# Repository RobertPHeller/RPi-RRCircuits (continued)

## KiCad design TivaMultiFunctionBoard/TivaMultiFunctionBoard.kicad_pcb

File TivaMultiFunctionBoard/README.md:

# TivaMultiFunctionBoard

This is a circuit board that supports a Tiva LaunchPad MCU to manage a range
of possible interlocking plants or other model railroad situations. It
contains four stall motor drivers with point sense, four CT Coil type
occupancy detectors, four Schmitt-Trigger inputs (for push buttons), four
driver outputs, 8 GPIO pins in a 5x2 header, and 16 PWM LED drivers. 
                                                  
The board contains these I/O sections:

- Four occupancy detectors.  These are current transformer based for DCC.
- Four stall-motor with point sense.
- Four Schmitt-Trigger inputs, typically for facia push buttons.
- Four driver outputs, typically for facia lamps (LEDs).
- Eight GPIO pins brought out to a 5x2 header.
- Sixteen PWM Led drivers.  These are meant to light lamps in signal heads. 

This board uses 24 GPIO pins and one I2C channel:

- **PD7** OD1
- **PF4** OD2
- **PA5** OD3
- **PB2** OD4
- **PC5** Motor1
- **PC6** Motor2
- **PC7** Motor3
- **PD6** Motor4
- **PF2** Points1
- **PF3** Points2
- **PB3** Points3
- **PC4** Points4
- **PD0** LED1
- **PD1** LED2
- **PD2** LED3
- **PD3** LED4
- **PE1** Button1
- **PE2** Button2
- **PE3** Button3
- **PF1** Button4
- **PE0** GPIO8
- **PF0** GPIO7
- **PB4** GPIO6
- **PB7** GPIO5
- **PB6** GPIO4
- **PA4** GPIO3
- **PA3** GPIO2
- **PA2** GPIO1
- **I2C1 Address 0x40** A PCA9685 16-channel, 12-bit PWM LED Controller

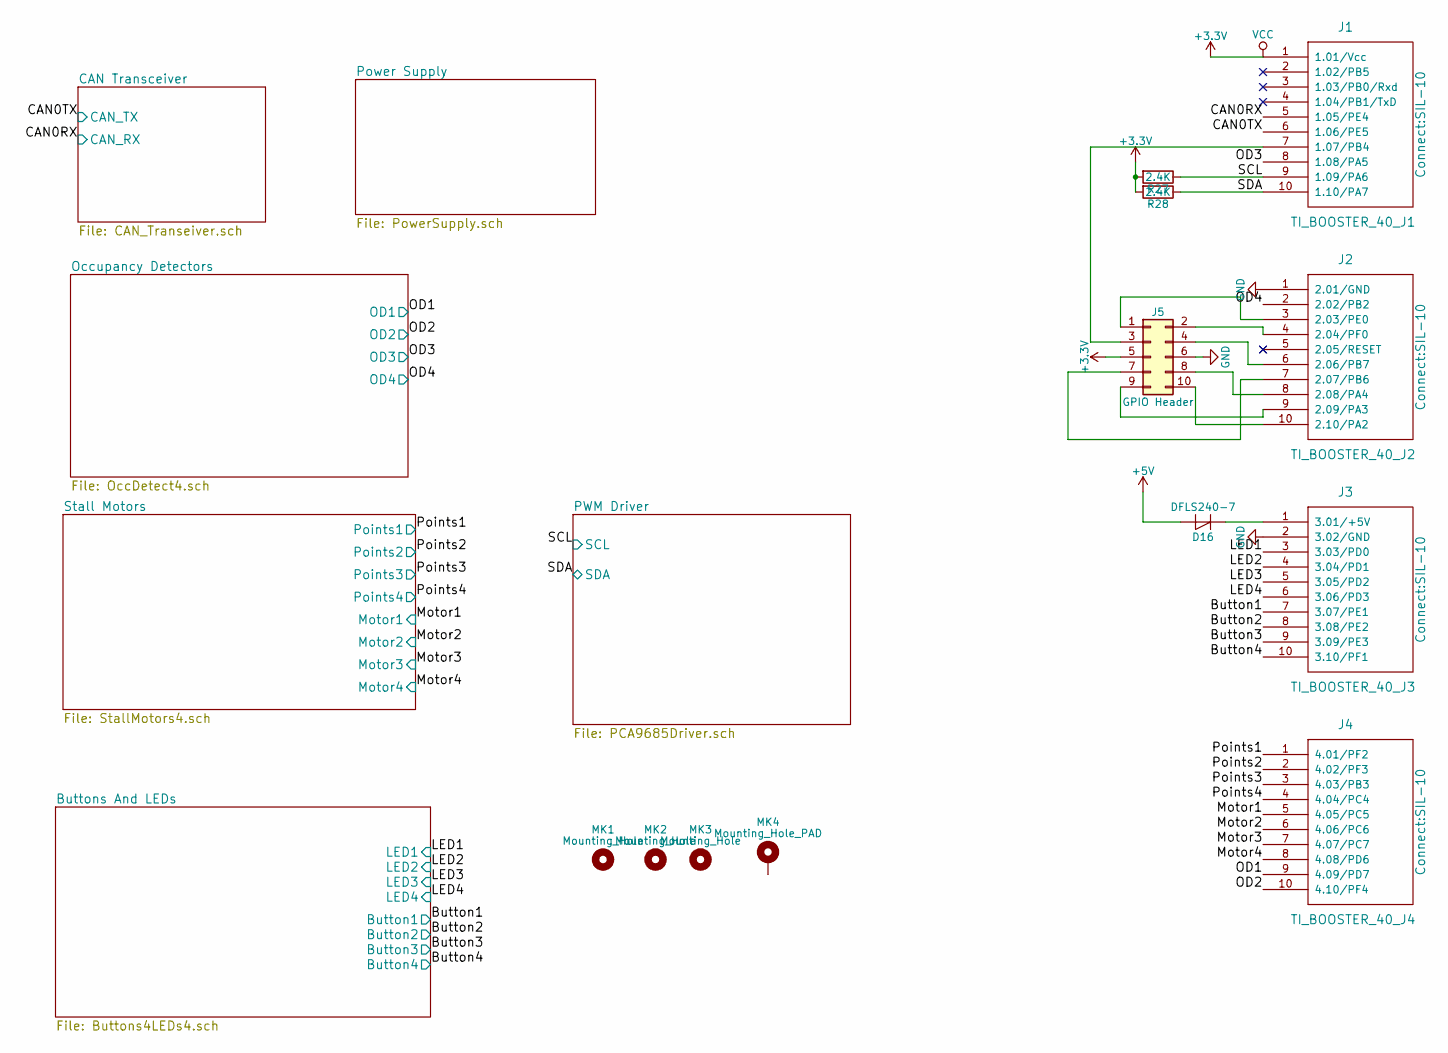
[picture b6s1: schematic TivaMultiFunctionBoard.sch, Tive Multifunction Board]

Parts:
D16: DFLS240-7; D_SMB; Mouser Part Number 621-DFLS240-7
J1: TI_BOOSTER_40_J1; SIL-10
J2: TI_BOOSTER_40_J2; SIL-10
J3: TI_BOOSTER_40_J3; SIL-10
J4: TI_BOOSTER_40_J4; SIL-10
J5: GPIO Header; IDC_Header_Straight_10pins
MK1, MK2, MK3: Mounting_Hole; MountingHole_3.2mm_M3
MK4: Mounting_Hole_PAD; MountingHole_3.2mm_M3_Pad
R27, R28: 2.4K; R_0603; Mouser Part Number 71-CRCW06032K40JN

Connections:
+5V: D16.2 (A); also elsewhere on the board
/Button1: J3.7 (3.07/PE1); also elsewhere on the board
/Button2: J3.8 (3.08/PE2); also elsewhere on the board
/Button3: J3.9 (3.09/PE3); also elsewhere on the board
/Button4: J3.10 (3.10/PF1); also elsewhere on the board
/CAN0RX: J1.5 (1.05/PE4); also elsewhere on the board
/CAN0TX: J1.6 (1.06/PE5); also elsewhere on the board
/LED1: J3.3 (3.03/PD0); also elsewhere on the board
/LED2: J3.4 (3.04/PD1); also elsewhere on the board
/LED3: J3.5 (3.05/PD2); also elsewhere on the board
/LED4: J3.6 (3.06/PD3); also elsewhere on the board
/Motor1: J4.5 (4.05/PC5); also elsewhere on the board
/Motor2: J4.6 (4.06/PC6); also elsewhere on the board
/Motor3: J4.7 (4.07/PC7); also elsewhere on the board
/Motor4: J4.8 (4.08/PD6); also elsewhere on the board
/OD1: J4.9 (4.09/PD7); also elsewhere on the board
/OD2: J4.10 (4.10/PF4); also elsewhere on the board
/OD3: J1.8 (1.08/PA5); also elsewhere on the board
/OD4: J2.2 (2.02/PB2); also elsewhere on the board
/Points1: J4.1 (4.01/PF2); also elsewhere on the board
/Points2: J4.2 (4.02/PF3); also elsewhere on the board
/Points3: J4.3 (4.03/PB3); also elsewhere on the board
/Points4: J4.4 (4.04/PC4); also elsewhere on the board
/SCL: J1.9 (1.09/PA6), R27.1; also elsewhere on the board
/SDA: J1.10 (1.10/PA7), R28.1; also elsewhere on the board
GND: J2.1 (2.01/GND), J3.2 (3.02/GND), J5.6; also elsewhere on the board
unnamed: D16.1 (K), J3.1 (3.01/+5V)
unnamed: J1.7 (1.07/PB4), J5.3
unnamed: J2.3 (2.03/PE0), J5.1
unnamed: J2.4 (2.04/PF0), J5.2
unnamed: J2.6 (2.06/PB7), J5.4
unnamed: J2.7 (2.07/PB6), J5.7
unnamed: J2.8 (2.08/PA4), J5.8
unnamed: J2.9 (2.09/PA3), J5.9
unnamed: J2.10 (2.10/PA2), J5.10

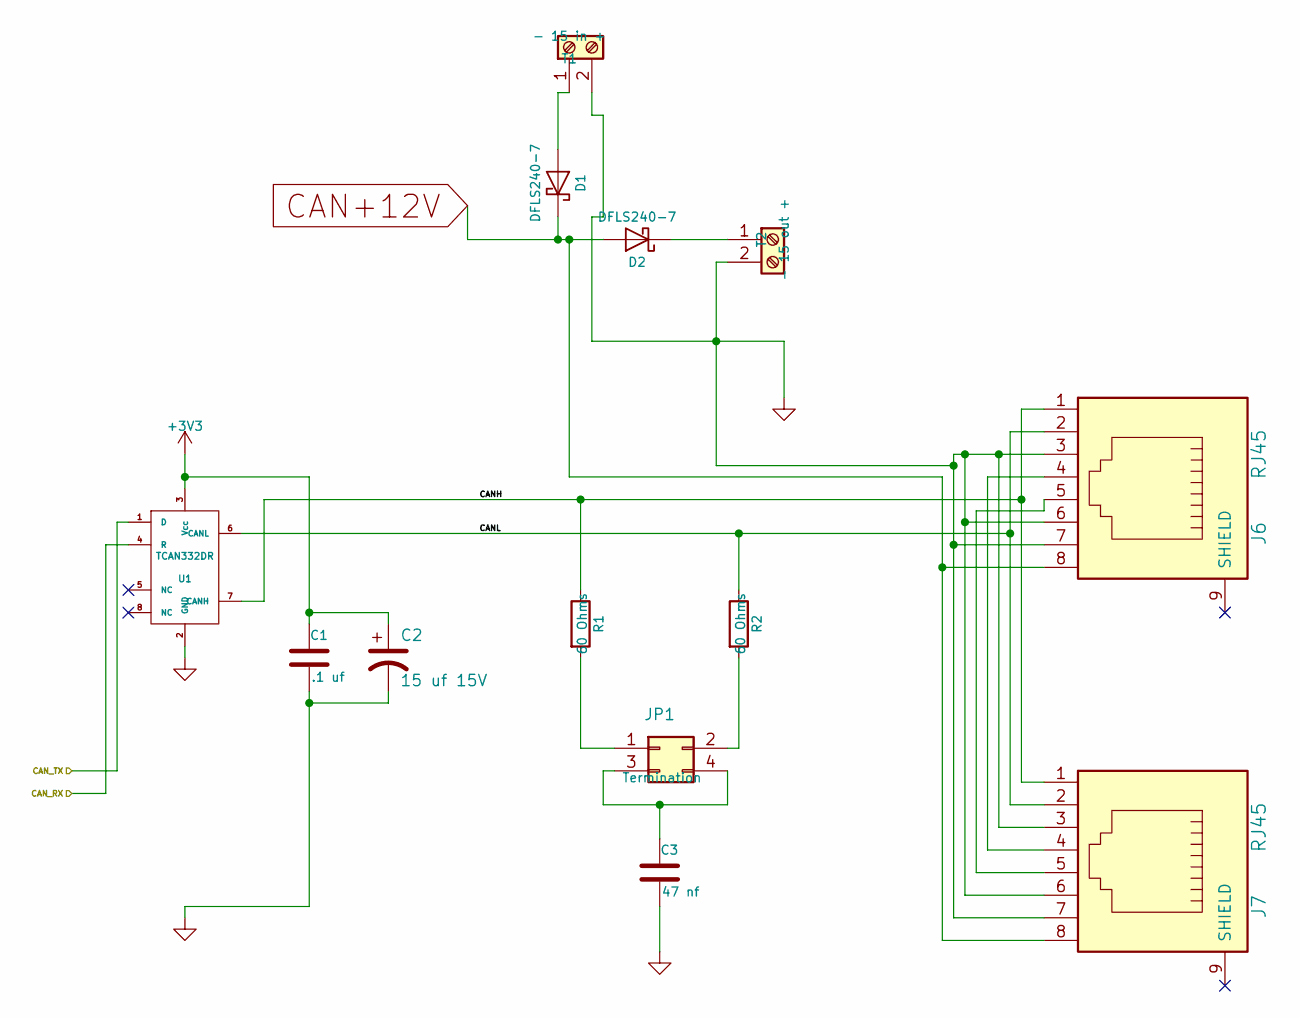
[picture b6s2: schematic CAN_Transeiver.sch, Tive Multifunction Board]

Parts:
C1: .1 uf; C_0603; Mouser Part Number 710-885012206095
C2: 15 uf 15V; CP_Elec_4x5.7; Mouser Part Number 647-UUD1C150MCL
C3: 47 nf; C_0603; Mouser Part Number 710-885012206093
D1, D2: DFLS240-7; D_SMB; Mouser Part Number 621-DFLS240-7
J6, J7: RJ45; RJ45_8N-S; Mouser Part Number 710-615008144221
JP1: Termination; Pin_Header_Straight_2x02_Pitch2.54mm; Mouser Part Number 649-67997-404HLF
R1, R2: 60 Ohms; R_1206; Mouser Part Number 71-CRCW120660R0KNAIF
T1: - 15 in +; TerminalBlock_Pheonix_MPT-2.54mm_2pol; Mouser Part Number 651-1725656
T2: - 15 out +; TerminalBlock_Pheonix_MPT-2.54mm_2pol; Mouser Part Number 651-1725656
U1: TCAN332DR; SOIC-8_3.9x4.9mm_Pitch1.27mm; Mouser Part Number 595-TCAN332DR

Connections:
/CAN0RX: U1.4 (R); also elsewhere on the board
/CAN0TX: U1.1 (D); also elsewhere on the board
/CAN Transceiver/CANH: J6.1, J7.1, R1.1, U1.7 (CANH)
/CAN Transceiver/CANL: J6.2, J7.2, R2.1, U1.6 (CANL)
GND: C1.2, C2.2, C3.2, J6.3, J6.6, J6.7, J7.3, J7.6, J7.7, T1.2, T2.2, U1.2 (GND); also elsewhere on the board
unnamed: C3.1, JP1.3, JP1.4
unnamed: D1.2 (A), T1.1
unnamed: D2.1 (K), T2.1
unnamed: J6.4, J7.4
unnamed: J6.5, J7.5
unnamed: JP1.1, R1.2
unnamed: JP1.2, R2.2

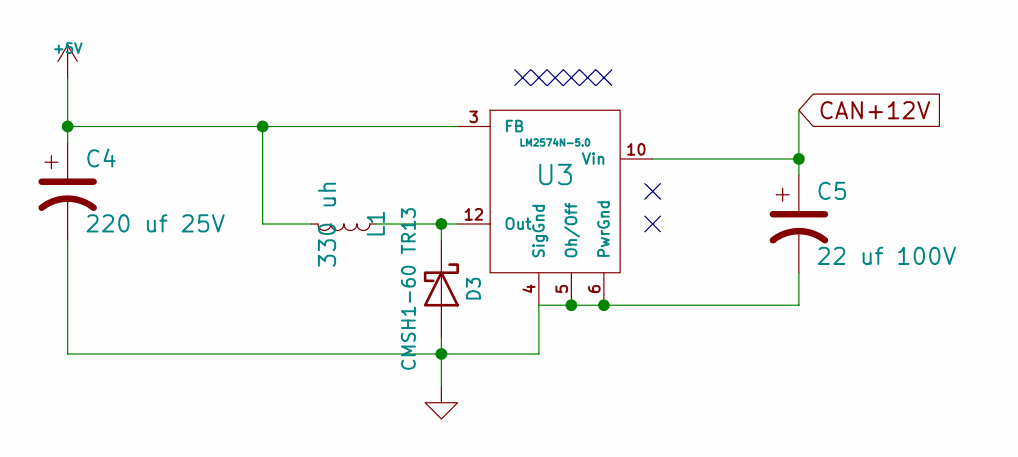
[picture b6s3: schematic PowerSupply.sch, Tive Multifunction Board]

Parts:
C4: 220 uf 25V; CP_Elec_8x10; Mouser Part Number 647-UWT1E221MNL1GS
C5: 22 uf 100V; CP_Elec_8x10; Mouser Part Number 647-UUX2A220MNL6GS
D3: CMSH1-60 TR13; D_SMB; Mouser Part Number 610-CMSH1-60TR13
L1: 330 uh; SRN1060; Mouser Part Number 652-SRN1060-331M
U3: LM2574N-5.0; SOIC-14_7.4x8.7mm_Pitch1.27mm; Mouser Part Number 926-LM2574N-5.0/NOPB

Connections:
+5V: C4.1, L1.2, U3.3 (FB); also elsewhere on the board
GND: C4.2, C5.2, D3.2 (A), U3.4 (SigGnd), U3.5 (Oh/Off), U3.6 (PwrGnd); also elsewhere on the board
unnamed: D3.1 (K), L1.1, U3.12 (Out)

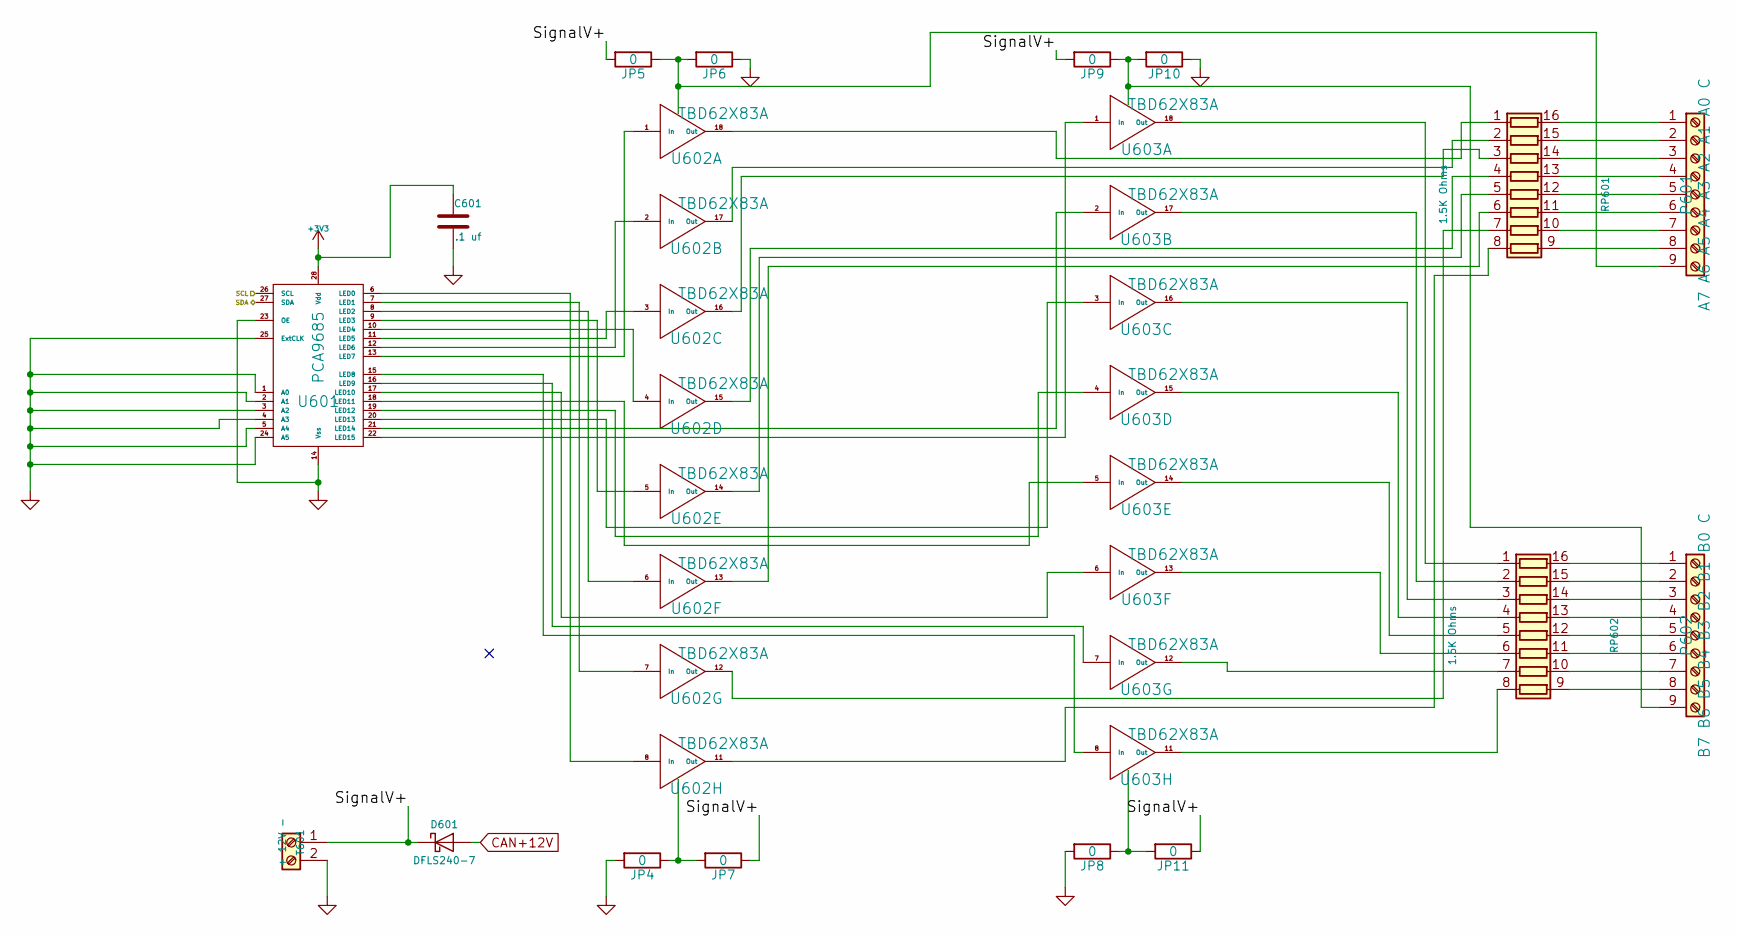
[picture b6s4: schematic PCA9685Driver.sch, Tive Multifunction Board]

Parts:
C601: .1 uf; C_0603; Mouser Part Number 710-885012206095
D601: DFLS240-7; D_SMB; Mouser Part Number 621-DFLS240-7
JP4, JP5, JP6, JP7, JP8, JP9, JP10, JP11: 0; R_1206; Mouser Part Number 71-CRCW12060000Z0EBC
P601: A7 A6 A5 A4 A3 A2 A1 A0 C; TerminalBlock_Pheonix_MPT-2.54mm_9pol; Mouser Part Number 651-1725724
P602: B7 B6 B5 B4 B3 B2 B1 B0 C; TerminalBlock_Pheonix_MPT-2.54mm_9pol; Mouser Part Number 651-1725724
RP601, RP602: 1.5K Ohms; 4816P; Mouser Part Number 652-4816P-T1LF-1.5K
T601: + 12V -; TerminalBlock_Pheonix_MPT-2.54mm_2pol; Mouser Part Number 651-1725656
U601: PCA9685; TSSOP-28_4.4x9.7mm_Pitch0.65mm; Mouser Part Number 771-PCA9685PW,118
U602, U603: TBD62X83A; SOIC-18W_7.5x11.6mm_Pitch1.27mm; Mouser Part Number 757-TBD62083AFG or 757-TBD62783AFG

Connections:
/PWM Driver/SignalV+: D601.1 (K), JP5.2, JP7.1, JP9.2, JP11.1, T601.1
/SCL: U601.26 (SCL); also elsewhere on the board
/SDA: U601.27 (SDA); also elsewhere on the board
GND: C601.2, JP4.2, JP6.1, JP8.2, JP10.1, T601.2, U601.1 (A0), U601.2 (A1), U601.3 (A2), U601.4 (A3), U601.5 (A4), U601.14 (Vss), U601.23 (OE), U601.24 (A5), U601.25 (ExtCLK); also elsewhere on the board
unnamed: JP4.1, JP7.2, U602.9 (IC)
unnamed: JP5.1, JP6.2, P601.9, U602.10 (OC)
unnamed: JP9.1, JP10.2, P602.9, U603.10 (OC)
unnamed: JP8.1, JP11.2, U603.9 (IC)
unnamed: P601.1, RP601.16 (R1.2)
unnamed: P601.2, RP601.15 (R2.2)
unnamed: P601.3, RP601.14 (R3.2)
unnamed: P601.4, RP601.13 (R4.2)
unnamed: P601.5, RP601.12 (R5.2)
unnamed: P601.6, RP601.11 (R6.2)
unnamed: P601.7, RP601.10 (R7.2)
unnamed: P601.8, RP601.9 (R8.2)
unnamed: P602.1, RP602.16 (R1.2)
unnamed: P602.2, RP602.15 (R2.2)
unnamed: P602.3, RP602.14 (R3.2)
unnamed: P602.4, RP602.13 (R4.2)
unnamed: P602.5, RP602.12 (R5.2)
unnamed: P602.6, RP602.11 (R6.2)
unnamed: P602.7, RP602.10 (R7.2)
unnamed: P602.8, RP602.9 (R8.2)
unnamed: RP601.1 (R1.1), U602.18 (Out)
unnamed: RP601.2 (R2.1), U602.17 (Out)
unnamed: RP601.3 (R3.1), U602.16 (Out)
unnamed: RP601.4 (R4.1), U602.15 (Out)
unnamed: RP601.5 (R5.1), U602.14 (Out)
unnamed: RP601.6 (R6.1), U602.13 (Out)
unnamed: RP601.7 (R7.1), U602.12 (Out)
unnamed: RP601.8 (R8.1), U602.11 (Out)
unnamed: RP602.1 (R1.1), U603.18 (Out)
unnamed: RP602.2 (R2.1), U603.17 (Out)
unnamed: RP602.3 (R3.1), U603.16 (Out)
unnamed: RP602.4 (R4.1), U603.15 (Out)
unnamed: RP602.5 (R5.1), U603.14 (Out)
unnamed: RP602.6 (R6.1), U603.13 (Out)
unnamed: RP602.7 (R7.1), U603.12 (Out)
unnamed: RP602.8 (R8.1), U603.11 (Out)
unnamed: U601.6 (LED0), U602.8 (In)
unnamed: U601.7 (LED1), U602.7 (In)
unnamed: U601.8 (LED2), U602.6 (In)
unnamed: U601.9 (LED3), U602.5 (In)
unnamed: U601.10 (LED4), U602.4 (In)
unnamed: U601.11 (LED5), U602.3 (In)
unnamed: U601.12 (LED6), U602.2 (In)
unnamed: U601.13 (LED7), U602.1 (In)
unnamed: U601.15 (LED8), U603.8 (In)
unnamed: U601.16 (LED9), U603.7 (In)
unnamed: U601.17 (LED10), U603.6 (In)
unnamed: U601.18 (LED11), U603.5 (In)
unnamed: U601.19 (LED12), U603.4 (In)
unnamed: U601.20 (LED13), U603.3 (In)
unnamed: U601.21 (LED14), U603.2 (In)
unnamed: U601.22 (LED15), U603.1 (In)

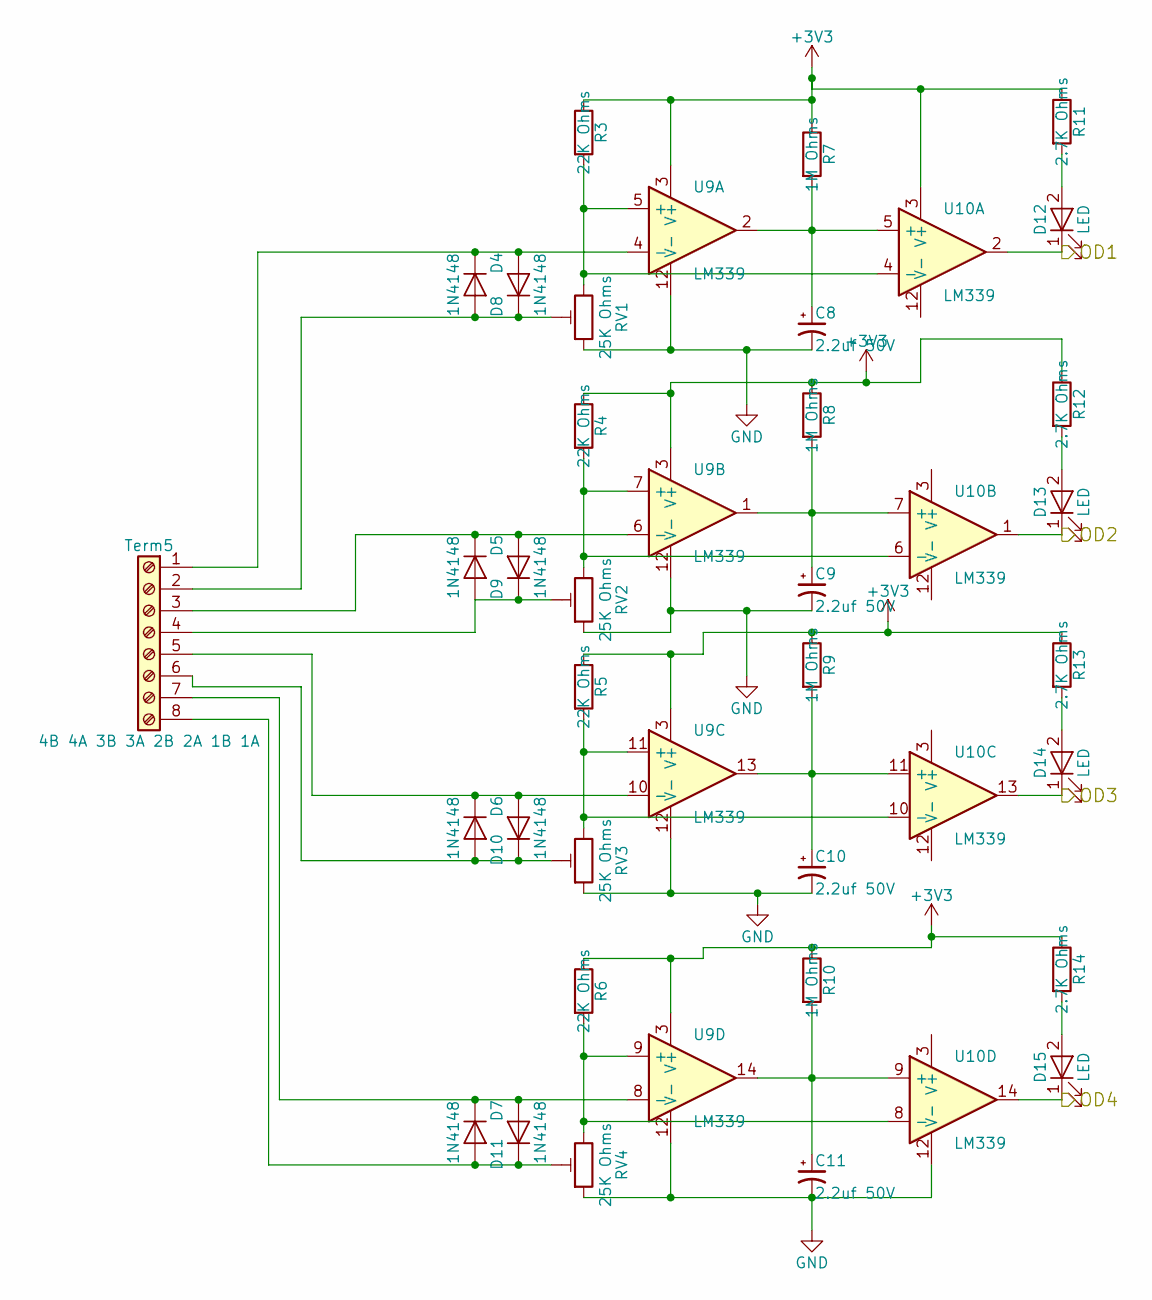
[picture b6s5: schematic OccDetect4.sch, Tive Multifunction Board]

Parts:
C8, C9, C10, C11: 2.2uf 50V; CP_Elec_4x5.7; Mouser Part Number 710-865080140002
D4, D5, D6, D7, D8, D9, D10, D11: 1N4148; D_SOD-123; Mouser Part Number 750-1N4148WS-HF
D12, D13, D14, D15: LED; LED_0603; Mouser Part Number 710-150060SS55040
R3, R4, R5, R6: 22K Ohms; R_0603; Mouser Part Number 71-RCG060322K0JNEA
R7, R8, R9, R10: 1M Ohms; R_0603; Mouser Part Number 71-CRCW06031M00JNEAC
R11, R12, R13, R14: 2.7K Ohms; R_0603; Mouser Part Number 71-CRCW06032K70JNEAC
RV1, RV2, RV3, RV4: 25K Ohms; Potentiometer_Trimmer_Bourns_3214J; Mouser Part Number 652-3314J-1-253E
Term5: 4B 4A 3B 3A 2B 2A 1B 1A; TerminalBlock_Pheonix_MPT-2.54mm_8pol; Mouser Part Number 651-1725711
U9, U10: LM339; SOIC-14_3.9x8.7mm_Pitch1.27mm

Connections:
/OD1: D12.1 (K), U10.2; also elsewhere on the board
/OD2: D13.1 (K), U10.1; also elsewhere on the board
/OD3: D14.1 (K), U10.13; also elsewhere on the board
/OD4: D15.1 (K), U10.14; also elsewhere on the board
GND: C8.2, C9.2, C10.2, C11.2, RV1.1, RV2.1, RV3.1, RV4.1, U9.12 (V-), U10.12 (V-); also elsewhere on the board
unnamed: C8.1, R7.2, U9.2, U10.5 (+)
unnamed: C9.1, R8.2, U9.1, U10.7 (+)
unnamed: C10.1, R9.2, U9.13, U10.11 (+)
unnamed: C11.1, R10.2, U9.14, U10.9 (+)
unnamed: D4.1 (K), D8.2 (A), Term5.1, U9.4 (-)
unnamed: D4.2 (A), D8.1 (K), RV1.2, Term5.2
unnamed: D5.1 (K), D9.2 (A), Term5.3, U9.6 (-)
unnamed: D5.2 (A), D9.1 (K), RV2.2, Term5.4
unnamed: D6.2 (A), D10.1 (K), RV3.2, Term5.6
unnamed: D6.1 (K), D10.2 (A), Term5.5, U9.10 (-)
unnamed: D7.2 (A), D11.1 (K), RV4.2, Term5.8
unnamed: D7.1 (K), D11.2 (A), Term5.7, U9.8 (-)
unnamed: D12.2 (A), R11.2
unnamed: D13.2 (A), R12.2
unnamed: D14.2 (A), R13.2
unnamed: D15.2 (A), R14.2
unnamed: R3.2, RV1.3, U9.5 (+), U10.4 (-)
unnamed: R4.2, RV2.3, U9.7 (+), U10.6 (-)
unnamed: R5.2, RV3.3, U9.11 (+), U10.10 (-)
unnamed: R6.2, RV4.3, U9.9 (+), U10.8 (-)

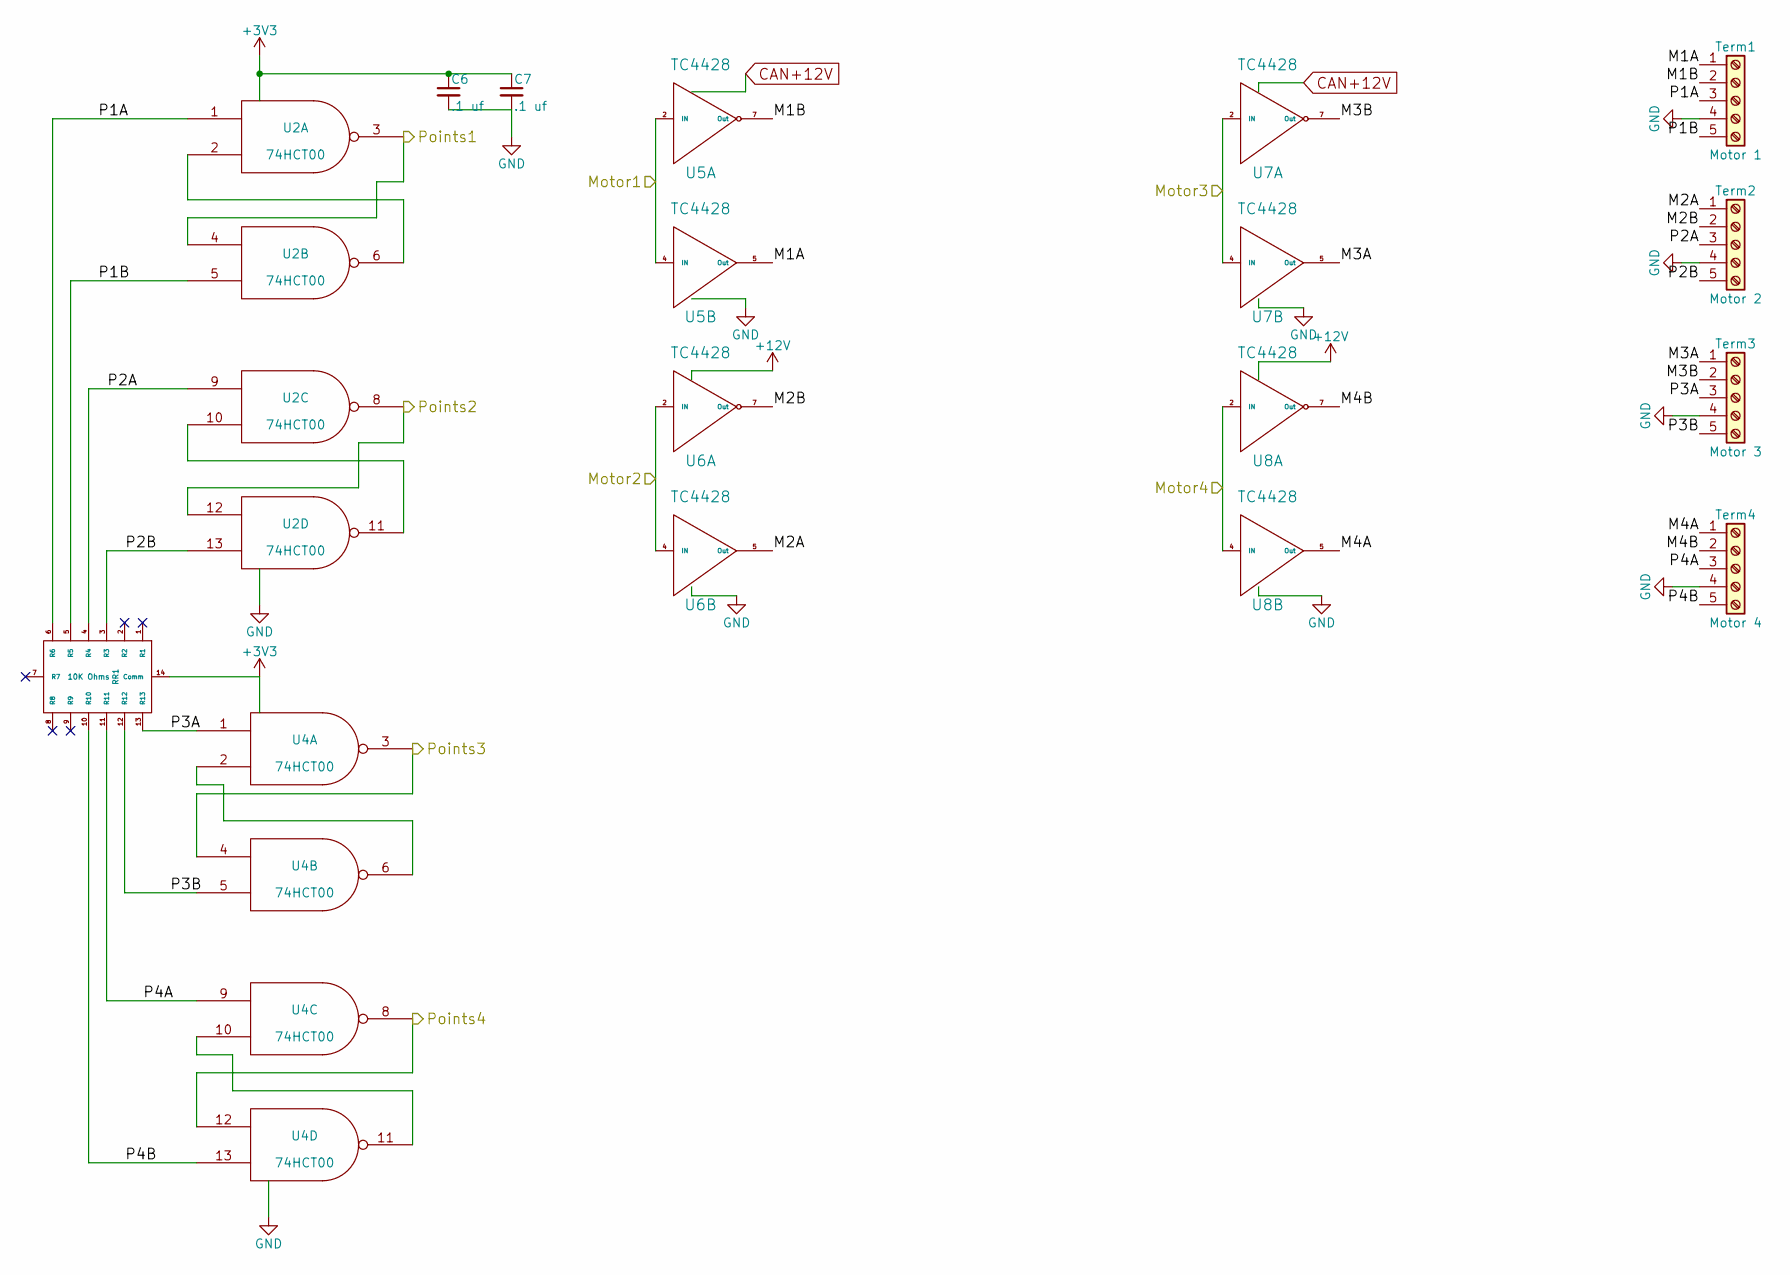
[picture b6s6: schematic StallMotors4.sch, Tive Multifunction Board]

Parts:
C6, C7: .1 uf; C_0603; Mouser Part Number 710-885012206095
RR1: 10K Ohms; 4814P; Mouser Part Number 652-4814P-2LF-10K
Term1: Motor 1; TerminalBlock_Pheonix_MPT-2.54mm_5pol; Mouser Part Number 651-1725685
Term2: Motor 2; TerminalBlock_Pheonix_MPT-2.54mm_5pol; Mouser Part Number 651-1725685
Term3: Motor 3; TerminalBlock_Pheonix_MPT-2.54mm_5pol; Mouser Part Number 651-1725685
Term4: Motor 4; TerminalBlock_Pheonix_MPT-2.54mm_5pol; Mouser Part Number 651-1725685
U2: 74HCT00; SOIC-14_3.9x8.7mm_Pitch1.27mm
U4: 74HCT00; SOIC-14_3.9x8.7mm_Pitch1.27mm; Mouser Part Number 595-SN74AHC00D
U5, U6, U7, U8: TC4428; SOIC-8_3.9x4.9mm_Pitch1.27mm; Mouser Part Number 579-TC4428VOA

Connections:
/Motor1: U5.2 (IN), U5.4 (IN); also elsewhere on the board
/Motor2: U6.2 (IN), U6.4 (IN); also elsewhere on the board
/Motor3: U7.2 (IN), U7.4 (IN); also elsewhere on the board
/Motor4: U8.2 (IN), U8.4 (IN); also elsewhere on the board
/Points1: U2.3, U2.4; also elsewhere on the board
/Points2: U2.8, U2.12; also elsewhere on the board
/Points3: U4.3, U4.4; also elsewhere on the board
/Points4: U4.8, U4.12; also elsewhere on the board
/Stall Motors/M1A: Term1.1, U5.5 (Out)
/Stall Motors/M1B: Term1.2, U5.7 (Out)
/Stall Motors/M2A: Term2.1, U6.5 (Out)
/Stall Motors/M2B: Term2.2, U6.7 (Out)
/Stall Motors/M3A: Term3.1, U7.5 (Out)
/Stall Motors/M3B: Term3.2, U7.7 (Out)
/Stall Motors/M4A: Term4.1, U8.5 (Out)
/Stall Motors/M4B: Term4.2, U8.7 (Out)
/Stall Motors/P1A: RR1.6 (R6), Term1.3, U2.1
/Stall Motors/P1B: RR1.5 (R5), Term1.5, U2.5
/Stall Motors/P2A: RR1.4 (R4), Term2.3, U2.9
/Stall Motors/P2B: RR1.3 (R3), Term2.5, U2.13
/Stall Motors/P3A: RR1.13 (R13), Term3.3, U4.1
/Stall Motors/P3B: RR1.12 (R12), Term3.5, U4.5
/Stall Motors/P4A: RR1.11 (R11), Term4.3, U4.9
/Stall Motors/P4B: RR1.10 (R10), Term4.5, U4.13
GND: C6.2, C7.2, Term1.4, Term2.4, Term3.4, Term4.4, U2.7 (GND), U4.7 (GND), U5.3 (GND), U6.3 (GND), U7.3 (GND), U8.3 (GND); also elsewhere on the board
unnamed: U2.2, U2.6
unnamed: U2.10, U2.11
unnamed: U4.2, U4.6
unnamed: U4.10, U4.11

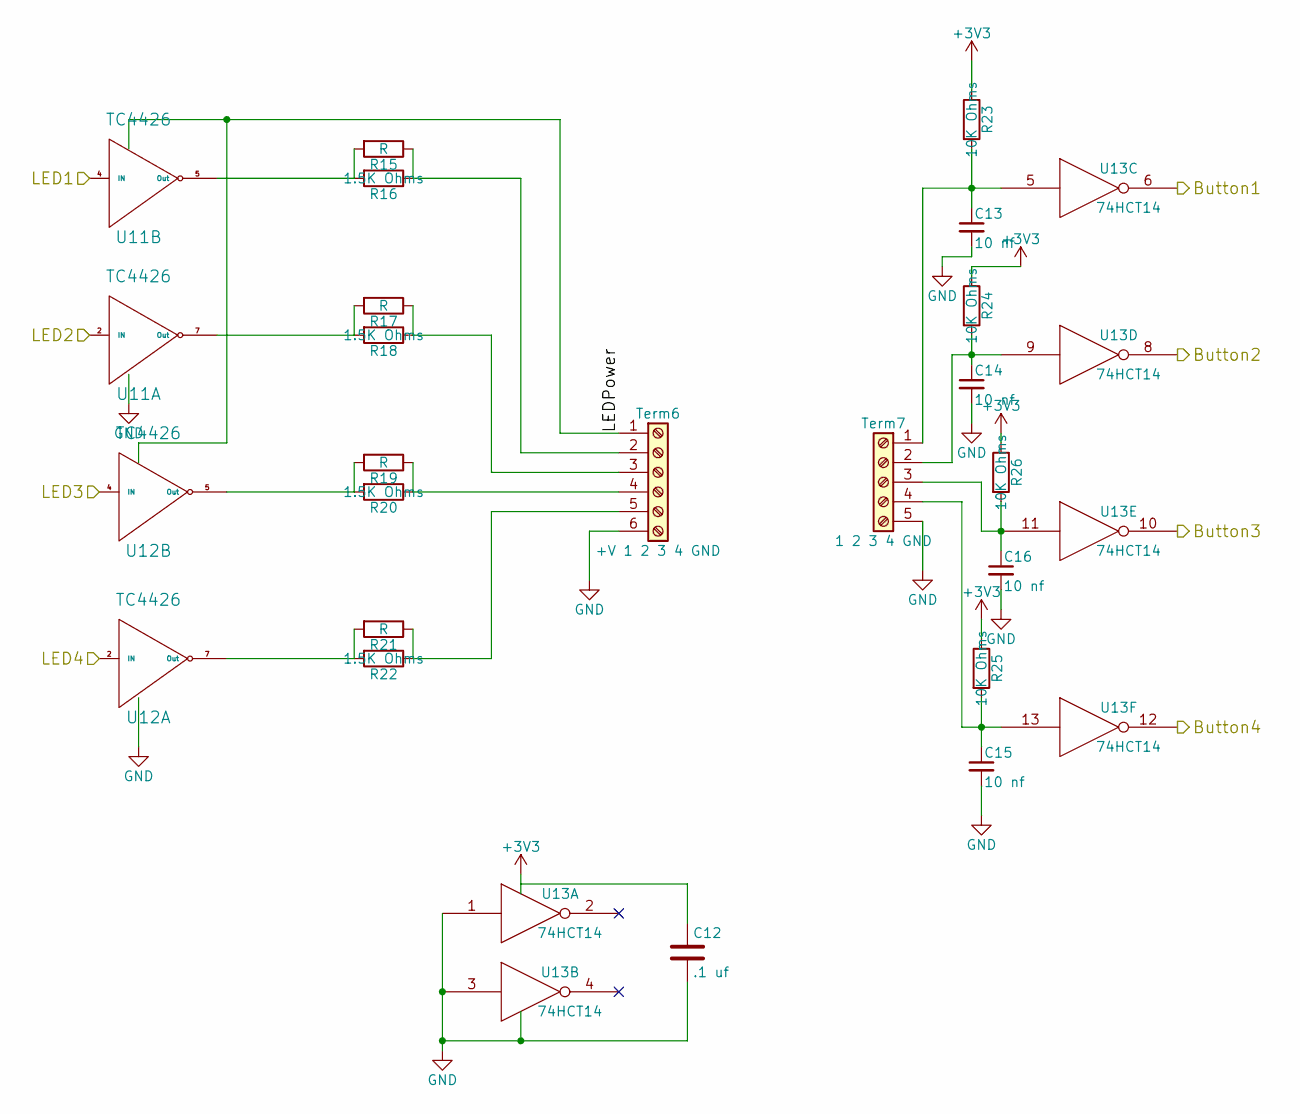
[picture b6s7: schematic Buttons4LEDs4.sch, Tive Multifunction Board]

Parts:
C12: .1 uf; C_0603
C13, C14, C15, C16: 10 nf; C_0603; Mouser Part Number 710-885382206002
R15, R17, R19, R21: R; R_Axial_DIN0207_L6.3mm_D2.5mm_P7.62mm_Horizontal
R16, R18, R20, R22: 1.5K Ohms; R_0603; Mouser Part Number 71-CRCW06031K50JNEAC
R23, R24, R25, R26: 10K Ohms; R_0603; Mouser Part Number 71-CRCW060310K0JNEBC
Term6: +V 1 2 3 4 GND; TerminalBlock_Pheonix_MPT-2.54mm_6pol; Mouser Part Number 651-1725698
Term7: 1 2 3 4 GND; TerminalBlock_Pheonix_MPT-2.54mm_5pol; Mouser Part Number 651-1725685
U11, U12: TC4426; SOIC-8_3.9x4.9mm_Pitch1.27mm
U13: 74HCT14; SOIC-14_3.9x8.7mm_Pitch1.27mm; Mouser Part Number 595-CD74HC14M

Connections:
/Button1: U13.6; also elsewhere on the board
/Button2: U13.8; also elsewhere on the board
/Button3: U13.10; also elsewhere on the board
/Button4: U13.12; also elsewhere on the board
/LED1: U11.4 (IN); also elsewhere on the board
/LED2: U11.2 (IN); also elsewhere on the board
/LED3: U12.4 (IN); also elsewhere on the board
/LED4: U12.2 (IN); also elsewhere on the board
GND: C12.2, C13.2, C14.2, C15.2, C16.2, Term6.6, Term7.5, U11.3 (GND), U12.3 (GND), U13.1, U13.3, U13.7 (GND); also elsewhere on the board
unnamed: C13.1, R23.2, Term7.1, U13.5
unnamed: C14.1, R24.2, Term7.2, U13.9
unnamed: C15.1, R25.2, Term7.4, U13.13
unnamed: C16.1, R26.2, Term7.3, U13.11
unnamed: R15.1, R16.1, Term6.2
unnamed: R15.2, R16.2, U11.5 (Out)
unnamed: R17.1, R18.1, Term6.3
unnamed: R17.2, R18.2, U11.7 (Out)
unnamed: R19.1, R20.1, Term6.4
unnamed: R19.2, R20.2, U12.5 (Out)
unnamed: R21.1, R22.1, Term6.5
unnamed: R21.2, R22.2, U12.7 (Out)
Vxx: Term6.1, U11.6 (Vxx), U12.6 (Vxx)

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
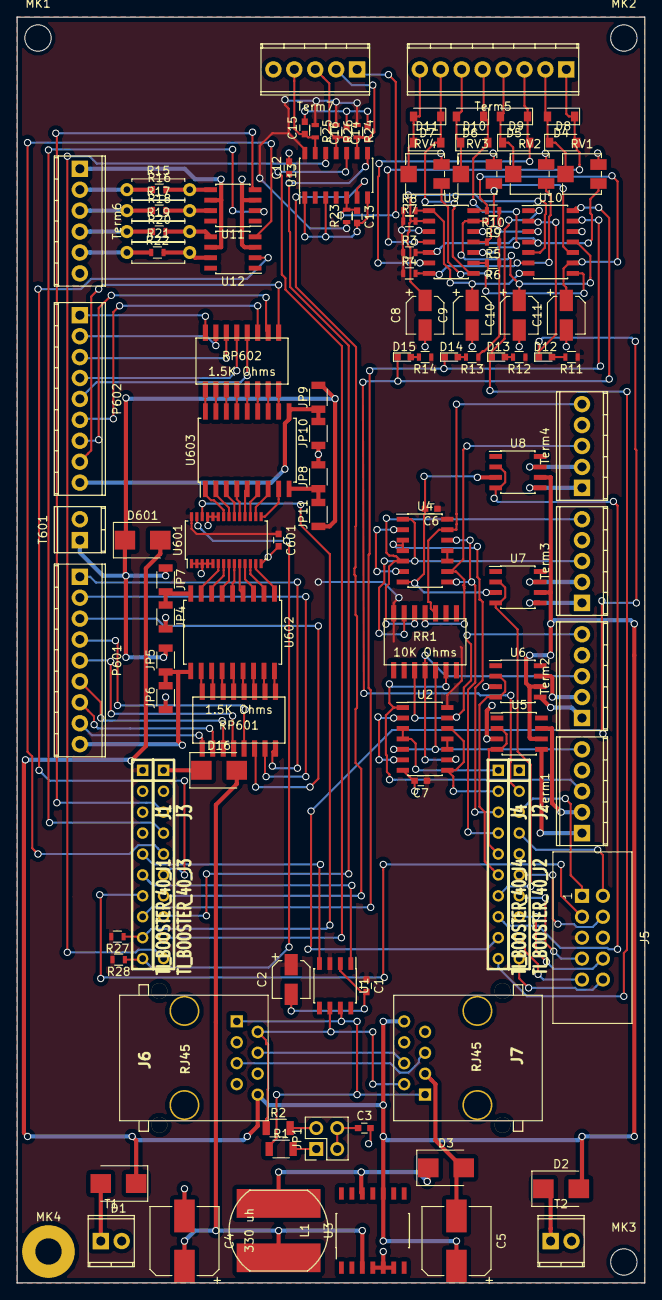
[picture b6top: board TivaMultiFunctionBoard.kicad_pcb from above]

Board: 2 copper layers, 76.2 x 153.7 mm, 118 parts (0 on the bottom side), 153 nets.
